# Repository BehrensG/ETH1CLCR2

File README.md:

<h1>ETH1CLCR2</h1>
LCR measurement card with Ethernet interface.

<h2>PCB Design</h2>

<p align="center">3D model rendition for PCB V1.0.</p>
<p align="center"></img></p>

<p align="center">Below are the images for the PCB V1.0. Mistake solved with botch wire.</p>

<p align="center"></img></p>
<p align="center"></img></p>
<p align="center"></img></p>

<h2>Tests</h2>
Some test measurements perform on passive components. 

>[!NOTE]
>The components where measured directly, not in a circuit. The cards was not calibrated.

<table align="center">
    <tr>
        <th>Type</th>
        <th>Component</th>
        <th>Value</th>
        <th>Component Tolerance</th>
        <th>Measurement</th>
    </tr>
    <tr>
        <td>Resistor</td>
        <td>WS21R000FEK</td>
        <td>2 Ω</td>
        <td>1%</td>
        <td>2.2352 Ω</td>
    </tr>
    <tr>
        <td>Resistor</td>
        <td>SR1206JR-7W3R3L</td>
        <td>3.3 Ω</td>
        <td>5%</td>
        <td>3.8283 Ω</td>
    </tr>
    <tr>
        <td>Resistor</td>
        <td>PTF5610K000AYEK</td>
        <td>10 kΩ</td>
        <td>0.05%</td>
        <td>10.01509 kΩ</td>
    </tr>
    <tr>
        <td>Resistor</td>
        <td>RN732BTTD9002B25</td>
        <td>90 kΩ</td>
        <td>0.1%</td>
        <td>90.02021 kΩ</td>
    </tr>
    <tr>
        <td>Resistor</td>
        <td>ERA-8VRB1003V</td>
        <td>100 kΩ</td>
        <td>0.1%</td>
        <td>100.294 kΩ</td>
    </tr>
    <tr>
        <td>Resistor</td>
        <td>HHV-50FR-52-10M</td>
        <td>10 MegΩ</td>
        <td>1%</td>
        <td>10.490122 MegΩ</td>
    </tr>
    <tr>
        <td>Inductor</td>
        <td>AISR-01-104J</td>
        <td>100 mH</td>
        <td>5%</td>
        <td>102.6 mH</td>
    </tr>
    <tr>
        <td>Capacitor</td>
        <td>KP1830310061</td>
        <td>10 nF</td>
        <td>1%</td>
        <td>10.07 nF</td>
    </tr>
    <tr>
        <td>Capacitor</td>
        <td>F461BC104F400A</td>
        <td>100 nF</td>
        <td>1%</td>
        <td>106 nF</td>
    </tr>
    <tr>
        <td>Capacitor</td>
        <td>C315C101F3G5TA</td>
        <td>0.1 nF</td>
        <td>1%</td>
        <td>0.1071 nF</td>
    </tr>
    <tr>
        <td>Capacitor</td>
        <td>D83W4010M01H</td>
        <td>10 uF</td>
        <td>3%</td>
        <td>10.152 uF</td>
    </tr>
    <tr>
        <td>Capacitor</td>
        <td>MPK1839510401</td>
        <td>1 uF</td>
        <td>1%</td>
        <td>1.0695 uF</td>
    </tr>
    <tr>
        <td>Capacitor</td>
        <td>EST108M063AM3AA</td>
        <td>1 mF</td>
        <td>20%</td>
        <td>1.1 mF</td>
    </tr>
    <tr>
        <td>Capacitor</td>
        <td>F463AG102F2K0A</td>
        <td>1 nF</td>
        <td>1%</td>
        <td>1.0459 nF</td>
    </tr>
    <tr>
        <td>Capacitor</td>
        <td>MKP1839310251</td>
        <td>10 nF</td>
        <td>1%</td>
        <td>10.0974 nF</td>
    </tr>
    <tr>
        <td>Capacitor</td>
        <td>MKP1837410011</td>
        <td>100 nF</td>
        <td>1%</td>
        <td>101.457 nF</td>
    </tr>
    <tr>
        <td>Capacitor</td>
        <td>23PS222</td>
        <td>2.2 nF</td>
        <td>5%</td>
        <td>2.2161 nF</td>
    </tr>
</table>

<h2>NOTES</h2>
The ETH1CLCR2 PCB works, but I don't recommend using this design. The design has mistakes and could be made simpler and better.

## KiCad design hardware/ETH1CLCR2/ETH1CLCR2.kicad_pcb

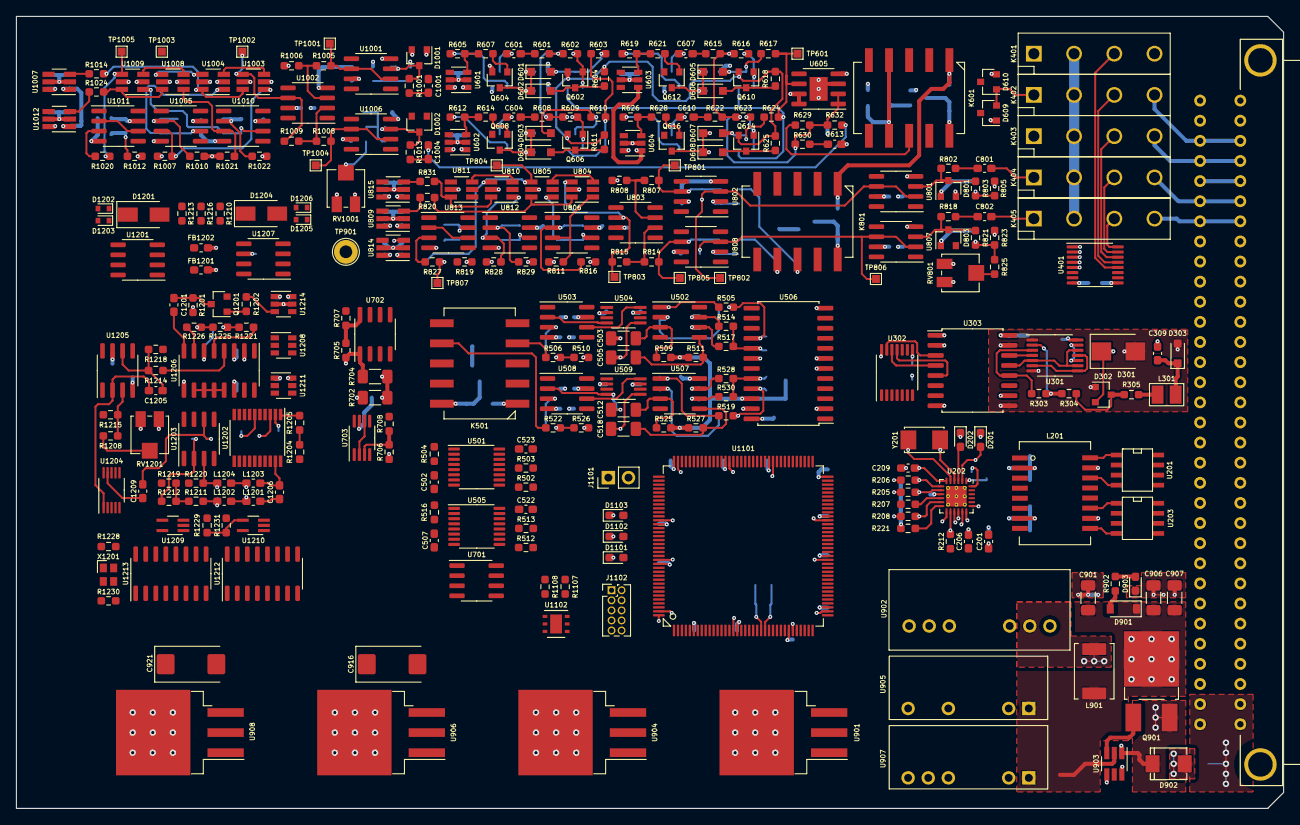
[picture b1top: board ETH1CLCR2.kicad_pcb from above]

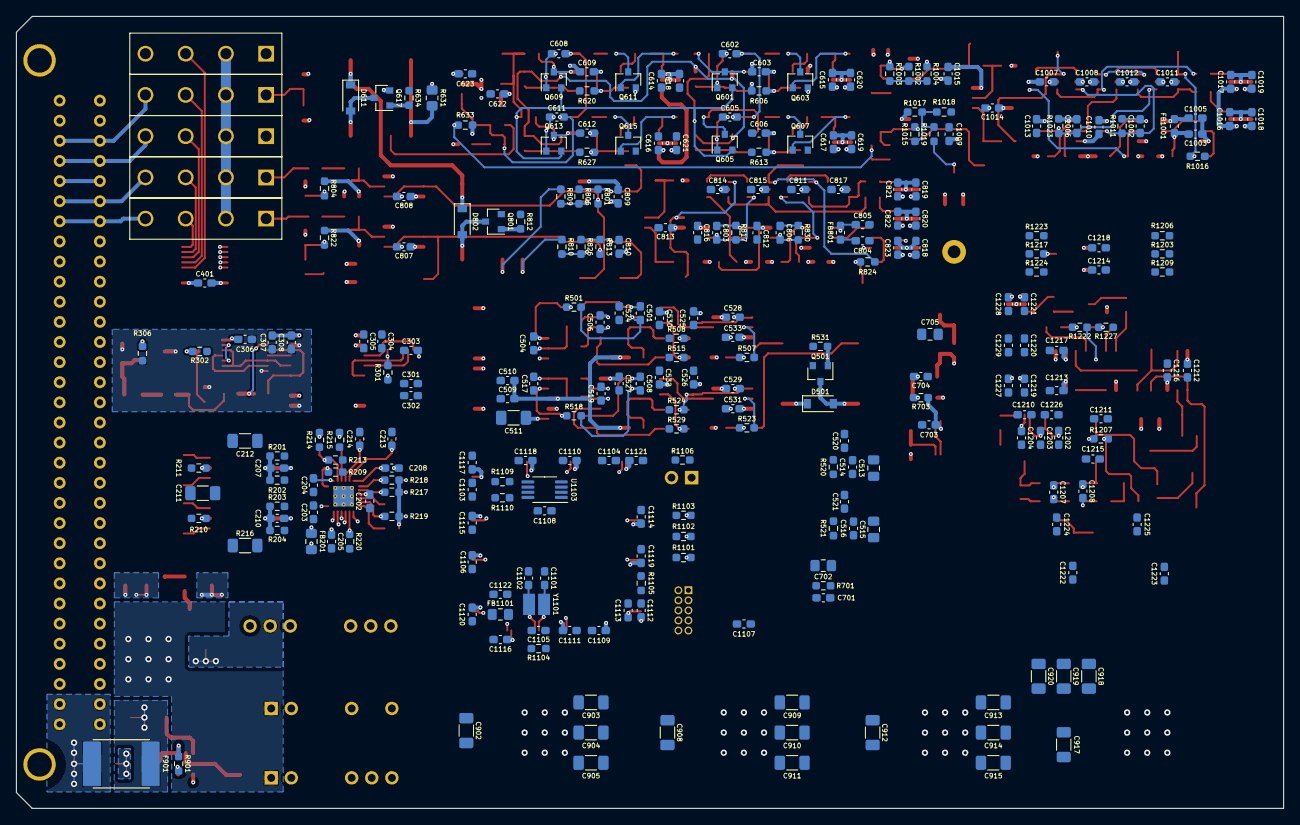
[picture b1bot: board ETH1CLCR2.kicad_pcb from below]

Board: 6 copper layers, 160.0 x 100.0 mm, 573 parts (268 on the bottom side), 354 nets.

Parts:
C201, C202, C204, C205, C206, C207, C210, C301, C303, C304, C306, C308, C520, C521, C522, C523, C524, C525, C526, C527, C528, C529, C530, C531, C532, C533, C603, C606, C609, C612, C614, C615, C616, C617, C618, C619, C620, C621, C622, C623, C807, C808, C809, C810, C811, C812, C813, C814, C815, C816, C817, C818, C819, C820, C821, C822, C823, C1007, C1008, C1009, C1010, C1011, C1012, C1013, C1014, C1015, C1016, C1017, C1018, C1019, C1105, C1107, C1108, C1109, C1110, C1111, C1112, C1113, C1114, C1115, C1116, C1117, C1118, C1119, C1120, C1121, C1203, C1210, C1211, C1212, C1213, C1214, C1215, C1216, C1217, C1218, C1219, C1220, C1221, C1222, C1223, C1224, C1225, C1226, C1227, C1228, C1229: 100n; C_0603_1608Metric_Pad1.08x0.95mm_HandSolder
C203, C209, C302, C305, C307, C401, C510, C514, C516, C701, C703, C704, C801, C802, C804, C805, C1001, C1003, C1004, C1005, C1106, C1122: 1u; C_0603_1608Metric_Pad1.08x0.95mm_HandSolder
C208, C613: 470p; C_0603_1608Metric_Pad1.08x0.95mm_HandSolder
C211, C212: 1n/1kV; C_1206_3216Metric_Pad1.33x1.80mm_HandSolder
C213, C214, C1101, C1102: 8p; C_0603_1608Metric_Pad1.08x0.95mm_HandSolder
C309: 47p; C_0603_1608Metric_Pad1.08x0.95mm_HandSolder
C501, C506, C508, C519: 470p/COG; C_0603_1608Metric_Pad1.08x0.95mm_HandSolder
C502, C507: 330p; C_0603_1608Metric_Pad1.08x0.95mm_HandSolder
C503, C505, C512, C518, C902, C903, C908, C909, C912, C913, C917, C918: 10u; C_1206_3216Metric_Pad1.33x1.80mm_HandSolder
C504, C517: 2700p/COG; C_0603_1608Metric_Pad1.08x0.95mm_HandSolder
C509, C1201: 10n; C_0603_1608Metric_Pad1.08x0.95mm_HandSolder
C511: 47u; C_1206_3216Metric_Pad1.33x1.80mm_HandSolder
C513, C515: 22u; C_0805_2012Metric_Pad1.18x1.45mm_HandSolder
C601, C604: 4n7; C_0603_1608Metric_Pad1.08x0.95mm_HandSolder
C602, C605, C607, C608, C610, C611, C803, C806, C1002, C1006: DNP; C_0603_1608Metric_Pad1.08x0.95mm_HandSolder
C702, C705: 10u; C_0805_2012Metric_Pad1.18x1.45mm_HandSolder
C901: 4u7; C_1206_3216Metric_Pad1.33x1.80mm_HandSolder
C904, C910, C914, C919: 1u; C_1206_3216Metric_Pad1.33x1.80mm_HandSolder
C905, C911, C915, C920: 100n; C_1206_3216Metric_Pad1.33x1.80mm_HandSolder
C906, C907: 4u7/50V; C_1206_3216Metric_Pad1.33x1.80mm_HandSolder
C916, C921: T521V107M016ATE050; CP_EIA-7343-20_Kemet-V_Pad2.25x2.55mm_HandSolder
C1103, C1104: 2u2; C_0603_1608Metric_Pad1.08x0.95mm_HandSolder
C1202, C1204, C1209: 4u7; C_0603_1608Metric_Pad1.08x0.95mm_HandSolder
C1205: 3p3/COG; C_0603_1608Metric_Pad1.08x0.95mm_HandSolder
C1206, C1208: 100p; C_0603_1608Metric_Pad1.08x0.95mm_HandSolder
C1207: 68p; C_0603_1608Metric_Pad1.08x0.95mm_HandSolder
D201: YELLOW; LED_0603_1608Metric_Pad1.05x0.95mm_HandSolder
D202, D1102: GREEN; LED_0603_1608Metric_Pad1.05x0.95mm_HandSolder
D301: SMBJ5.0A; D_SMB
D302: BAV99; SOT-23
D303: SD36C-01FTG; D_SOD-323_HandSoldering
D501, D611, D802: 1N4148W; D_SOD-123
D601, D602, D603, D604, D605, D606, D607, D608: BAS16J; D_SOD-323_HandSoldering
D609, D610, D801, D803, D1001, D1002: BAV199; SOT-23
D901: MMSZ5249B; D_SOD-123
D902: SM6T30AY; DO_214AA_REV
D903, D1101: RED; LED_0603_1608Metric_Pad1.05x0.95mm_HandSolder
D1103: BLUE; LED_0603_1608Metric_Pad1.05x0.95mm_HandSolder
D1201, D1204: BYG20J; D_SMA
D1202, D1203, D1205, D1206: BZX584C5V6; D_SOD-523
F901: MF-LSMF185/33X; Fuse_SMD2920
FB201, FB1101: 742792031; L_0805_2012Metric_Pad1.15x1.40mm_HandSolder
FB801, FB1001: BLM18TG102TN1D; L_0603_1608Metric_Pad1.05x0.95mm_HandSolder
FB1201, FB1202: BLM18SP601SZ1D; L_0603_1608Metric_Pad1.05x0.95mm_HandSolder
J401: C64AC; Socket_DIN41612-CaseC1-AC-Male-64Pin-2rows
J1101: Conn_02x01; PinHeader_1x02_P2.54mm_Vertical
J1102: 20021111-00010T4LF; PinHeader_2x05_P1.27mm_Vertical
K401, K402, K403, K404, K405: HE3621A0510; HE360_x-5050462-8
K501, K601, K801: TQ2SA-5V; SA
L201: 749010012A
L301: CW252016-R33G; CW252016
L901: PM1608S-100M-RC; PM1608S
L1201, L1202, L1203, L1204: CBMF1608T100K; L_0603_1608Metric_Pad1.05x0.95mm_HandSolder
Q501, Q603, Q607, Q611, Q615, Q617, Q801: BC847; SOT-23
Q601, Q602, Q605, Q606, Q609, Q610, Q613, Q614: MMBFJ309LT1G; SOT-23
Q604, Q608, Q612, Q616: BC857; SOT-23
Q901: IRFR5410; TO-252-2_Rectifier
Q1201: FDV301N; SOT-23
R201, R202, R203, R204: 49R9; R_0603_1608Metric_Pad0.98x0.95mm_HandSolder
R205, R206, R208, R212, R1227: 33; R_0603_1608Metric_Pad0.98x0.95mm_HandSolder
R207, R213, R217, R218, R219, R220, R301, R502, R503, R509, R511, R512, R513, R525, R527, R606, R613, R620, R627, R634, R812, R1104, R1105, R1106: 10k; R_0603_1608Metric_Pad0.98x0.95mm_HandSolder
R209: 12k1; R_0603_1608Metric_Pad0.98x0.95mm_HandSolder
R210, R211: 75/1%; R_0603_1608Metric_Pad0.98x0.95mm_HandSolder
R214, R215: 270; R_0603_1608Metric_Pad0.98x0.95mm_HandSolder
R216: 1M/1kV; R_1206_3216Metric_Pad1.30x1.75mm_HandSolder
R221: 1k5; R_0603_1608Metric_Pad0.98x0.95mm_HandSolder
R302, R820, R831, R1014, R1024, R1228: 1k; R_0603_1608Metric_Pad0.98x0.95mm_HandSolder
R303: 14k7; R_0603_1608Metric_Pad0.98x0.95mm_HandSolder
R304, R819, R1012, R1206, R1222, R1223: 100; R_0603_1608Metric_Pad0.98x0.95mm_HandSolder
R305: 47; R_0603_1608Metric_Pad0.98x0.95mm_HandSolder
R306: 51R1; R_0603_1608Metric_Pad0.98x0.95mm_HandSolder
R501, R517, R518, R530: 634; R_0603_1608Metric_Pad0.98x0.95mm_HandSolder
R504, R516, R632: 0; R_0603_1608Metric_Pad0.98x0.95mm_HandSolder
R505, R514, R519, R528: 91; R_0603_1608Metric_Pad0.98x0.95mm_HandSolder
R506, R510, R522, R526, R616: 10k/.1%; R_0603_1608Metric_Pad0.98x0.95mm_HandSolder
R507, R523: 300; R_0603_1608Metric_Pad0.98x0.95mm_HandSolder
R508, R515, R524, R529, R901, R1201, R1208: 100k; R_0603_1608Metric_Pad0.98x0.95mm_HandSolder
R520, R521, R701: 0R22; R_0603_1608Metric_Pad0.98x0.95mm_HandSolder
R531, R605, R607, R612, R614, R619, R621, R626, R628: 10K; R_0603_1608Metric_Pad0.98x0.95mm_HandSolder
R601, R608: 33/.1%; R_0603_1608Metric_Pad0.98x0.95mm_HandSolder
R602, R629, R802, R818, R1001, R1013: 100/.1%; R_0603_1608Metric_Pad0.98x0.95mm_HandSolder
R603, R604, R610, R611, R617, R618, R624, R625, R803, R821, R1002, R1015: 1Meg; R_0603_1608Metric_Pad0.98x0.95mm_HandSolder
R609, R807, R808, R814, R815, R1005, R1006, R1008, R1009: 1k/.1%; R_0603_1608Metric_Pad0.98x0.95mm_HandSolder
R615, R622, R633, R801, R813, R824, R1016: DNP; R_0603_1608Metric_Pad0.98x0.95mm_HandSolder
R623, R811, R828, R1007, R1021: 100k/.1%; R_0603_1608Metric_Pad0.98x0.95mm_HandSolder
R630: 47/.1%; R_0603_1608Metric_Pad0.98x0.95mm_HandSolder
R631: 0R1; R_0805_2012Metric_Pad1.20x1.40mm_HandSolder
R702: 3R3/.5W; R_1206_3216Metric_Pad1.30x1.75mm_HandSolder
R703: 10; R_0603_1608Metric_Pad0.98x0.95mm_HandSolder
R704: 33/.5W; R_1206_3216Metric_Pad1.30x1.75mm_HandSolder
R705: 220/.1%; R_0603_1608Metric_Pad0.98x0.95mm_HandSolder
R706, R708, R827, R1020: 3k3/.1%; R_0603_1608Metric_Pad0.98x0.95mm_HandSolder
R707: 1k1/.1%; R_0603_1608Metric_Pad0.98x0.95mm_HandSolder
R804, R805, R816, R822, R823, R829, R1003, R1004, R1010, R1017, R1018, R1022: 2k/.1%; R_0603_1608Metric_Pad0.98x0.95mm_HandSolder
R806, R826: 1k8/.1%; R_0603_1608Metric_Pad0.98x0.95mm_HandSolder
R809, R810: 200/.1%; R_0603_1608Metric_Pad0.98x0.95mm_HandSolder
R817, R830, R1011, R1023: 18k/.1%; R_0603_1608Metric_Pad0.98x0.95mm_HandSolder
R825, R1019: 47k/.1%; R_0603_1608Metric_Pad0.98x0.95mm_HandSolder
R902, R1209, R1219, R1224: 330; R_0603_1608Metric_Pad0.98x0.95mm_HandSolder
R1101, R1103, R1203, R1217, R1218: 680; R_0603_1608Metric_Pad0.98x0.95mm_HandSolder
R1102: 560; R_0603_1608Metric_Pad0.98x0.95mm_HandSolder
R1107, R1108, R1109, R1110, R1202: 4k7; R_0603_1608Metric_Pad0.98x0.95mm_HandSolder
R1204: 6k8; R_0603_1608Metric_Pad0.98x0.95mm_HandSolder
R1205: 2k; R_0603_1608Metric_Pad0.98x0.95mm_HandSolder
R1207: 820; R_0603_1608Metric_Pad0.98x0.95mm_HandSolder
R1210, R1213, R1216: 150; R_0603_1608Metric_Pad0.98x0.95mm_HandSolder
R1211, R1212, R1215, R1220, R1226: 200; R_0603_1608Metric_Pad0.98x0.95mm_HandSolder
R1214, R1221: 220; R_0603_1608Metric_Pad0.98x0.95mm_HandSolder
R1225, R1229, R1230, R1231: 68; R_0603_1608Metric_Pad0.98x0.95mm_HandSolder
RV801, RV1001: 3314J-1-203E; Potentiometer_Bourns_3314J_Vertical
RV1201: 3314J-1-104E; Potentiometer_Bourns_3314J_Vertical
TP601, TP801, TP802, TP803, TP804, TP805, TP806, TP807, TP1001, TP1002, TP1003, TP1004, TP1005: TestPoint; TestPoint_Pad_1.0x1.0mm
TP901: TestPoint; TestPoint_Loop_D2.60mm_Drill1.6mm_Beaded
U201, U203: LC03-3.3; SO8E
U202: LAN8742A; QFN-24-1EP_4x4mm_P0.5mm_EP2.6x2.6mm_ThermalVias
U301: 74AC125; TSSOP-14_4.4x5mm_P0.65mm
U302: TXB0104PW; TSSOP-14_4.4x5mm_P0.65mm
U303: ADuM5402; SOIC-16W_7.5x10.3mm_P1.27mm
U401: ULN2003A; TSSOP-16_4.4x5mm_P0.65mm
U501, U505: ADS8681PWR; TSSOP-16_4.4x5mm_P0.65mm
U502, U507: AD8656; SOIC-8_3.9x4.9mm_P1.27mm
U503, U508: OP1177AR; SOIC-8_3.9x4.9mm_P1.27mm
U504, U509: AD8476_MSOP; MSOP-8_3x3mm_P0.65mm
U506: CS5361; SOIC-24W_7.5x15.4mm_P1.27mm
U601, U602, U603, U604, U1208, U1211, U1214: SN74LVC1T45DBV; SOT-23-6
U605: ADA4817-1ARDZ; SOIC-8-1EP_3.9x4.9mm_P1.27mm_EP2.29x3mm
U701: REF5040ID; SOIC-8_3.9x4.9mm_P1.27mm
U702: TL431BCDE4; SOIC-8_3.9x4.9mm_P1.27mm
U703: MCP6L91RT-EMS; MSOP-8_3x3mm_P0.65mm
U801, U807, U813, U1001, U1006, U1011: MCP6L91RT-ESN; SOIC-8_3.9x4.9mm_P1.27mm
U802, U803, U806, U808, U812, U1002, U1005, U1010: MCP661; SOIC-8_3.9x4.9mm_P1.27mm
U804, U805, U810, U811, U1003, U1004, U1008, U1009: SN74LVC1G3157; SOT-23-6_Handsoldering
U809, U814, U815, U1007, U1012: SN74LVC1T45DBV; SOT-23-6_Handsoldering
U901: TLV1117-33; TO-263-3_TabPin2
U902: NCS3S1205SC; NCS3
U903: MAX5902; SOT-23-6_Handsoldering
U904, U906: TLV1117-50; TO-263-3_TabPin2
U905: NMK2409SAC; NMK_SINGLE
U907: NMK2409SC; NMK_DUAL
U908: LM2990SX-5.0; TO-263-3_TabPin2
U1101: STM32H743ZI; TQFP-144_20x20mm_P0.5mm
U1102: HDC1080; Texas_PWSON-N6
U1103: 24LC08B-E/MS; MSOP-8_3x3mm_P0.65mm
U1201, U1207: LMH6639; SOIC-8_3.9x4.9mm_P1.27mm
U1202: AD9834; TSSOP-20_4.4x6.5mm_P0.65mm
U1203, U1205: AD8038; SOIC-8_3.9x4.9mm_P1.27mm
U1204: DAC7811; VSSOP-10_3x3mm_P0.5mm
U1206: DG409; SOIC-16_3.9x9.9mm_P1.27mm
U1209: 74AHC1G14; SOT-353_SC-70-5_Handsoldering
U1210: 74AUP1G79; SOT-353_SC-70-5_Handsoldering
U1212, U1213: 74AC161; SOIC-16_3.9x9.9mm_P1.27mm
X1201: 830208220601; IQXO-791
Y201: NX5032GA-25.000M-LN-CD-1; NX5032GA
Y1101: NX3225GD-8MHZ; NX3225GD

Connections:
+1V5: R808.1, R811.2, R816.2, R828.2, R829.2, R1006.1, R1007.2, R1010.2, R1021.2, R1022.2, U703.2, U703.6
+3.3VP: C705.1, R704.1, R705.1, R706.1, R805.1, R823.1, R1004.1, R1018.1, RV801.1, RV1001.1, U702.1
+3V3: C201.1, C202.1, C301.1, C302.1, C522.1, C523.1, C618.1, C619.1, C620.1, C621.1, C818.1, C819.1, C820.1, C903.1, C904.1, C905.1, C1018.1, C1019.1, C1106.1, C1107.1, C1108.1, C1109.1, C1110.1, C1111.1, C1112.1, C1113.1, C1114.1, C1115.1, C1116.1, C1117.1, C1118.1, C1119.1, C1120.1, C1121.1, C1222.1, C1223.1, C1224.1, C1225.1, C1226.1, C1227.1, C1228.1, C1229.1, D1101.2, D1102.2, D1103.2, FB201.2, FB1101.2, J1102.1, R217.1, R218.1, R219.1, R220.1, R221.1, R301.1, R502.1, R503.1, R512.1, R513.1, R702.1, R1104.1, R1106.2, R1107.1, R1108.1, R1109.1, R1110.1, R1228.1, U202.9, U302.1, U501.16, U505.16, U506.2, U506.6, U506.8, U506.12, U601.6, U602.6, U603.6, U604.6, U809.6, U814.6, U815.6, U901.2, U1007.6, U1012.6, U1101.6, U1101.17, U1101.30, U1101.39, U1101.52, U1101.62, U1101.72, U1101.84, U1101.95, U1101.108, U1101.121, U1101.131, U1101.143, U1101.144, U1102.5, U1103.8, U1202.5, U1204.8, U1208.6, U1209.5, U1210.5, U1211.6, U1212.1, U1212.7, U1212.10, U1212.16, U1213.1, U1213.3, U1213.6, U1213.7, U1213.16, U1214.6, X1201.4
+4V: R701.1, U501.4, U505.4, U701.6
+5V: C303.1, C304.1, C305.1, C401.1, C520.1, C521.1, C614.1, C615.1, C616.1, C617.1, C821.1, C822.1, C823.1, C909.1, C910.1, C911.1, C1016.1, C1017.1, C1219.1, C1220.1, C1221.1, D501.1, D611.1, D802.1, K401.2, K402.2, K403.2, K404.2, K405.2, K501.1, K601.1, K801.1, U302.14, U303.1, U401.9, U501.2, U505.2, U506.19, U601.1, U602.1, U603.1, U604.1, U701.2, U809.1, U814.1, U815.1, U904.2, U1007.1, U1012.1, U1208.1, U1211.1, U1214.1
+5VA: C524.1, C525.1, C526.1, C527.1, C528.1, C529.1, C622.1, C807.1, C808.1, C809.1, C810.1, C811.1, C812.1, C813.1, C814.1, C815.1, C816.1, C817.1, C913.1, C914.1, C915.1, C916.1, C1007.1, C1008.1, C1009.1, C1010.1, C1011.1, C1012.1, C1013.1, C1014.1, C1015.1, C1210.1, C1211.1, C1212.1, C1213.1, C1214.1, D801.2, D803.2, D1001.2, D1002.2, D1201.1, D1202.1, D1203.1, FB1201.1, Q604.2, Q608.2, Q612.2, Q616.2, R819.2, R1012.2, R1201.1, RV1201.1, U502.8, U503.7, U504.2, U507.8, U508.7, U509.2, U605.7, U605.8, U801.7, U802.7, U803.7, U804.5, U805.5, U806.7, U807.7, U808.7, U810.5, U811.5, U812.7, U906.2, U1001.7, U1002.7, U1003.5, U1004.5, U1005.7, U1006.7, U1008.5, U1009.5, U1010.7, U1201.8, U1202.4, U1203.7, U1205.7, U1206.2, U1206.14, U1207.8
+5V_TRIG: C306.1, C307.1, C308.1, R302.1, U301.14, U303.10, U303.16
+24V: F901.2, J401.A31, J401.A32, J401.C31, J401.C32
-5VA: C530.1, C531.1, C532.1, C533.1, C623.1, C918.2, C919.2, C920.2, C921.2, C1215.1, C1216.1, C1217.1, C1218.1, D1204.2, D1205.2, D1206.2, FB1202.1, R606.2, R613.2, R620.2, R627.2, RV1201.3, U503.4, U504.7, U508.4, U509.7, U605.4, U908.3, U1203.4, U1205.4, U1206.3
/ADC/ADC1_IIN: K501.2, R504.2
/ADC/ADC1_MISO: R513.2, U505.13, U1101.112
/ADC/ADC1_MOSI: U501.10, U1101.113
/ADC/ADC1_RVS1: U501.15, U1101.114
/ADC/ADC1_RVS2: U505.15, U1101.115
/ADC/ADC1_SCLK: U501.12, U505.12, U1101.111
/ADC/ADC1_VIN: K501.9, R516.2
/ADC/ADC1_~CS: U501.11, U505.11, U1101.110
/ADC/ADC2_IIN: K501.4, R506.2
/ADC/ADC2_VIN: K501.7, R522.2
/ADC/ADC_IIN: K501.3, U1011.2, U1011.6
/ADC/ADC_VIN: K501.8, U813.2, U813.6
/ADC/CAP1: R520.1, U501.6
/ADC/CAP2: R521.1, U505.6
/ADC/DDS_CLK: R1231.1, U506.5
/ADC/VQ: C509.1, C510.1, R509.2, R511.2, R525.2, R527.2, U506.22
/Connector/A: J401.A2, J401.C2, K401.4
/Connector/B: J401.A3, J401.C3, K402.4
/Connector/C: J401.A4, J401.C4, K403.4
/Connector/CXN_REL1: U401.5, U1101.122
/Connector/CXN_REL2: U401.4, U1101.119
/Connector/CXN_REL3: U401.3, U1101.118
/Connector/CXN_REL4: U401.2, U1101.117
/Connector/CXN_REL5: U401.1, U1101.116
/Connector/D: J401.A5, J401.C5
/Connector/E: J401.A6, J401.C6, K404.4
/Connector/EXT_TRIG: C309.1, D303.1, J401.A16, L301.1
/Connector/F: J401.A7, J401.C7, K405.4
/Connector/H_CUR: K401.1, R1210.1, R1213.1, R1216.1
/Connector/H_POT: C801.2, K404.1
/Connector/L_CUR: D609.2, D610.1, K402.1, K601.3
/Connector/L_POT: C802.2, K405.1
/Connector/RX+: J401.A20, U203.8
/Connector/RX-: J401.A21, U203.5
/Connector/TX+: J401.C20, U201.8
/Connector/TX-: J401.C21, U201.5
/Current Diff Amp/CUR_IN: C1001.2, Q602.2, Q606.2, Q610.2, Q614.2, R604.1, R611.1, R618.1, R625.1
/Current Diff Amp/CUR_ZERO: C1004.2, R632.1, R633.1
/Current Diff Amp/IDIFF0: U1012.4, U1101.139
/Current Diff Amp/IDIFF1: U1007.4, U1101.140
/DDS/A0: U1206.1, U1208.3
/DDS/A1: U1206.16, U1211.3
/DDS/DDS_CS: U1101.73, U1202.15
/DDS/DDS_SCLK: U1101.74, U1202.14
/DDS/DDS_SDATA: U1101.76, U1202.13
/DDS/LPF: R1202.2, U1214.3
/DDS/MCLK: R1229.1, U1202.8
/DDS/MDAC_CS: U1101.40, U1204.6
/DDS/MDAC_SCK: U1101.41, U1204.4
/DDS/MDAC_SDIN: U1101.123, U1204.5
/DDS/MDAC_SDO: U1101.42, U1204.7
/DDS/~DDS_DIV10: U1213.4, U1213.5
/Ethernet/ETH_RXN: L201.8, R204.2, U202.22
/Ethernet/ETH_RXP: L201.6, R203.2, U202.23
/Ethernet/ETH_TXN: L201.3, R202.2, U202.20
/Ethernet/ETH_TXP: L201.1, R201.2, U202.21
/Ethernet/MODE0: R205.1, R217.2, U202.8
/Ethernet/MODE1: R206.1, R218.2, U202.7
/Ethernet/MODE2: R208.1, R219.2, U202.11
/Ethernet/NRST: C1105.1, J1102.10, R1104.2, U202.15, U1101.25
/Ethernet/REFCLK0: R212.1, R220.2, U202.14
/Ethernet/REF_CLK: R212.2, U1101.35
/Ethernet/RMII_CRS_DV: R208.2, U1101.43
/Ethernet/RMII_MDC: U202.13, U1101.27
/Ethernet/RMII_MDIO: R221.2, U202.12, U1101.36
/Ethernet/RMII_RXD0: R205.2, U1101.44
/Ethernet/RMII_RXD1: R206.2, U1101.45
/Ethernet/RMII_TXD0: U202.17, U1101.128
/Ethernet/RMII_TXD1: U202.18, U1101.129
/Ethernet/RMII_TXEN: U202.16, U1101.126
/I/V Converter/IRR0: R634.2, U1101.133
/I/V Converter/IRR1: U601.4, U1101.134
/I/V Converter/IRR2: U602.4, U1101.135
/I/V Converter/IRR3: U603.4, U1101.136
/I/V Converter/IRR4: U604.4, U1101.137
/MCU/EEPROM_SCL: R1110.2, U1101.81, U1103.6
/MCU/EEPROM_SDA: R1109.2, U1101.82, U1103.5
/MCU/EEPROM_WP: U1101.80, U1103.7
/MCU/MCU_DEFAULT: J1101.1, R1106.1, U1101.37
/MCU/MCU_VDDA: C1122.1, FB1101.1, U1101.32, U1101.33
/MCU/SENS_SCL: R1107.2, U1101.100, U1102.6
/MCU/SENS_SDA: R1108.2, U1101.99, U1102.1
/MCU/TCK_SWCLK: J1102.4, U1101.109
/MCU/TMS_SWDIO: J1102.2, U1101.105
/MCU/TRIG_EN: U302.2, U1101.92
/MCU/TRIG_IN: U302.4, U1101.88
/MCU/TRIG_OUT: U302.3, U1101.91
/MCU/VDIFF0: U814.4, U1101.46
/MCU/VDIFF1: U815.4, U1101.47
/MCU/VDIFF2: U809.4, U1101.48
/Trigger/EXT_TRIG_SIGN: R303.1, U301.3, U303.12
/Trigger/TRIG_OUT_EN: U301.4, U301.10, U301.13, U303.14
/Trigger/TRIG_OUT_SIGN: U301.5, U301.9, U301.12, U303.13
Earth: C211.2, C212.1, J401.A18, J401.A22, J401.C18, J401.C22, R216.1
GND: C201.2, C202.2, C203.2, C204.2, C205.2, C206.2, C207.2, C208.2, C209.2, C210.2, C212.2, C213.2, C214.2, C301.2, C302.2, C303.2, C304.2, C305.2, C401.2, C502.2, C507.2, C509.2, C510.2, C511.2, C513.2, C514.2, C515.2, C516.2, C520.2, C521.2, C522.2, C523.2, C524.2, C525.2, C526.2, C527.2, C528.2, C529.2, C530.2, C531.2, C532.2, C533.2, C603.2, C606.2, C609.2, C612.2, C613.2, C614.2, C615.2, C616.2, C617.2, C618.2, C619.2, C620.2, C621.2, C622.2, C623.2, C701.2, C702.2, C703.2, C704.2, C705.2, C804.1, C805.1, C807.2, C808.2, C809.2, C810.2, C811.2, C812.2, C813.2, C814.2, C815.2, C816.2, C817.2, C818.2, C819.2, C820.2, C821.2, C822.2, C823.2, C902.2, C903.2, C904.2, C905.2, C908.2, C909.2, C910.2, C911.2, C912.2, C913.2, C914.2, C915.2, C916.2, C917.1, C918.1, C919.1, C920.1, C921.1, C1003.1, C1005.1, C1007.2, C1008.2, C1009.2, C1010.2, C1011.2, C1012.2, C1013.2, C1014.2, C1015.2, C1016.2, C1017.2, C1018.2, C1019.2, C1101.2, C1102.2, C1103.2, C1104.2, C1105.2, C1106.2, C1107.2, C1108.2, C1109.2, C1110.2, C1111.2, C1112.2, C1113.2, C1114.2, C1115.2, C1116.2, C1117.2, C1118.2, C1119.2, C1120.2, C1121.2, C1122.2, C1202.2, C1203.1, C1204.1, C1210.2, C1211.2, C1212.2, C1213.2, C1214.2, C1215.2, C1216.2, C1217.2, C1218.2, C1219.2, C1220.2, C1221.2, C1222.2, C1223.2, C1224.2, C1225.2, C1226.2, C1227.2, C1228.2, C1229.2, D609.1, D610.2, D801.1, D803.1, D1001.1, D1002.1, D1202.2, D1203.2, D1205.1, D1206.1, J1101.2, J1102.3, J1102.5, K403.1, Q501.2, Q603.2, Q607.2, Q611.2, Q615.2, Q617.2, Q801.2, Q1201.2, R207.2, R209.1, R213.2, R214.2, R215.2, R216.2, R508.2, R510.1, R515.2, R524.2, R526.1, R529.2, R631.2, R633.2, R707.2, R708.2, R804.2, R822.2, R1003.2, R1017.2, R1105.2, R1204.1, R1209.2, R1215.2, R1219.2, R1220.2, R1224.2, R1227.2, RV801.3, RV1001.3, TP901.1, U202.25, U302.7, U303.2, U303.8, U401.8, U501.1, U501.3, U501.5, U501.8, U502.4, U504.1, U504.3, U505.1, U505.3, U505.5, U505.8, U506.7, U506.18, U506.23, U507.4, U509.1, U509.3, U601.2, U601.5, U602.2, U602.5, U603.2, U603.5, U604.2, U604.5, U605.3, U605.9, U701.4, U702.2, U702.3, U702.6, U702.7, U703.4, U801.4, U802.4, U803.4, U804.2, U805.2, U806.4, U807.4, U808.4, U809.2, U809.5, U810.2, U811.2, U812.4, U813.4, U814.2, U814.5, U815.2, U815.5, U901.1, U902.7, U904.1, U905.5, U906.1, U907.6, U908.1, U1001.4, U1002.4, U1003.2, U1004.2, U1005.4, U1006.4, U1007.2, U1007.5, U1008.2, U1009.2, U1010.4, U1011.4, U1012.2, U1012.5, U1101.16, U1101.31, U1101.38, U1101.51, U1101.61, U1101.83, U1101.94, U1101.107, U1101.120, U1101.130, U1102.2, U1103.1, U1103.2, U1103.3, U1103.4, U1202.7, U1202.9, U1202.10, U1202.11, U1202.12, U1202.17, U1202.18, U1204.2, U1204.3, U1206.9, U1206.15, U1208.2, U1208.5, U1209.3, U1210.3, U1211.2, U1211.5, U1212.3, U1212.8, U1213.8, U1214.2, U1214.5, X1201.2
GNDPWR: C901.2, C906.2, C907.2, D902.2, D903.1, J401.A27, J401.A28, J401.C27, J401.C28, U902.1, U903.4, U905.2, U907.2
GND_TRIG: C306.2, C307.2, C308.2, D301.2, D302.1, D303.2, J401.C16, R306.2, U301.1, U301.7, U303.9, U303.15
unnamed: C208.1, C209.1, U202.6
unnamed: C211.1, R210.2, R211.2
unnamed: C213.1, U202.5, Y201.2
unnamed: C214.1, U202.4, Y201.1
unnamed: C309.2, R306.1
unnamed: C501.1, R505.2, U502.1
unnamed: C501.2, R501.2, U502.2
unnamed: C502.1, R504.1, U501.7
unnamed: C503.1, R509.1, U502.3
unnamed: C503.2, R508.1, U503.2, U504.4
unnamed: C504.1, R501.1, R505.1, U506.16
unnamed: C504.2, R514.1, R517.1, U506.17
unnamed: C505.1, R511.1, U502.5
unnamed: C505.2, R515.1, U504.5
unnamed: C506.1, R514.2, U502.7
unnamed: C506.2, R517.2, U502.6
unnamed: C507.1, R516.1, U505.7
unnamed: C508.1, R519.2, U507.1
unnamed: C508.2, R518.2, U507.2
unnamed: C511.1, U506.24
unnamed: C512.1, R525.1, U507.3
unnamed: C512.2, R524.1, U508.2, U509.4
unnamed: C513.1, C514.1, R520.2
unnamed: C515.1, C516.1, R521.2
unnamed: C517.1, R518.1, R519.1, U506.21
unnamed: C517.2, R528.1, R530.1, U506.20
unnamed: C518.1, R527.1, U507.5
unnamed: C518.2, R529.1, U509.5
unnamed: C519.1, R528.2, U507.7
unnamed: C519.2, R530.2, U507.6
unnamed: C601.1, R601.2
unnamed: C601.2, Q603.3
unnamed: C602.1, Q601.1, Q602.1, R602.1
unnamed: C602.2, C605.2, C608.2, C611.2, K601.2, R601.1, R602.2, R608.1, R609.2, R615.1, R616.2, R622.1, R623.2, R629.1, R630.1, R632.2, U605.1, U605.2
unnamed: C603.1, D601.1, D602.1, Q604.3, R606.1
unnamed: C604.1, R608.2
unnamed: C604.2, Q607.3
unnamed: C605.1, Q605.1, Q606.1, R609.1
unnamed: C606.1, D603.1, D604.1, Q608.3, R613.1
unnamed: C607.1, R615.2
unnamed: C607.2, Q611.3
unnamed: C608.1, Q609.1, Q610.1, R616.1
unnamed: C609.1, D605.1, D606.1, Q612.3, R620.1
unnamed: C610.1, R622.2
unnamed: C610.2, Q615.3
unnamed: C611.1, Q613.1, Q614.1, R623.1
unnamed: C612.1, D607.1, D608.1, Q616.3, R627.1
unnamed: C613.1, R630.2
unnamed: C701.1, U701.5
unnamed: C702.1, R701.2
unnamed: C703.1, R703.1, U703.7
unnamed: C704.1, R702.2, R703.2, R704.2
unnamed: C801.1, R802.2
unnamed: C802.1, R818.2
unnamed: C803.1, R817.1, U805.1, U806.6
unnamed: C803.2, R816.1, R817.2, U806.2
unnamed: C804.2, FB801.1, R819.1
unnamed: C805.2, FB801.2, U813.7
unnamed: C806.1, R830.1, U811.1, U812.6
unnamed: C806.2, R829.1, R830.2, U812.2
unnamed: C901.1, C906.1, C907.1, D901.1, L901.1, Q901.2, U903.2, U905.1, U907.1
unnamed: C902.1, U901.3, U902.6
unnamed: C908.1, U904.3, U905.7
unnamed: C912.1, U906.3, U907.7
unnamed: C917.2, U907.5, U908.2
unnamed: C1001.1, R1001.2
unnamed: C1002.1, R1011.1, U1004.1, U1005.6
unnamed: C1002.2, R1010.1, R1011.2, U1005.2
unnamed: C1003.2, FB1001.1, R1012.1
unnamed: C1004.1, R1013.2
unnamed: C1005.2, FB1001.2, U1011.7
unnamed: C1006.1, R1023.1, U1009.1, U1010.6
unnamed: C1006.2, R1022.1, R1023.2, U1010.2
unnamed: C1101.1, U1101.23, Y1101.1
unnamed: C1102.1, U1101.24, Y1101.2
unnamed: C1103.1, U1101.71
unnamed: C1104.1, U1101.106
unnamed: C1201.1, U1201.3, U1206.8, U1207.3
unnamed: C1201.2, Q1201.3, R1201.2
unnamed: C1202.1, U1202.6
unnamed: C1203.2, U1202.3
unnamed: C1204.2, U1202.2
unnamed: C1205.1, R1214.2, R1218.2, U1204.10, U1205.6
unnamed: C1205.2, U1204.1, U1205.2
unnamed: C1206.1, L1201.1, U1202.20
unnamed: C1206.2, L1203.1, U1202.19
unnamed: C1207.1, L1201.2, L1202.1
unnamed: C1207.2, L1203.2, L1204.1
unnamed: C1208.1, L1202.2, R1211.2
unnamed: C1208.2, L1204.2, R1220.1, U1203.3
unnamed: C1209.1, U1204.9
unnamed: C1209.2, R1207.1, U1203.6
unnamed: D201.1, R214.1
unnamed: D201.2, R213.1, U202.2
unnamed: D202.1, R215.1
unnamed: D202.2, U202.3
unnamed: D301.1, D302.2, R302.2
unnamed: D302.3, R304.2, R305.1, U301.6, U301.8, U301.11
unnamed: D501.2, K501.10, Q501.3
unnamed: D601.2, Q601.3, R603.2
unnamed: D602.2, Q602.3, R604.2
unnamed: D603.2, Q605.3, R610.2
unnamed: D604.2, Q606.3, R611.2
unnamed: D605.2, Q609.3, R617.2
unnamed: D606.2, Q610.3, R618.2
unnamed: D607.2, Q613.3, R624.2
unnamed: D608.2, Q614.3, R625.2
unnamed: D611.2, K601.10, Q617.3
unnamed: D801.3, R802.1, R803.2, U801.3
unnamed: D802.2, K801.10, Q801.3
unnamed: D803.3, R818.1, R821.2, U807.3
unnamed: D901.2, R902.1
unnamed: D902.1, F901.1, Q901.3, R901.1, U903.1
unnamed: D903.2, R902.2
unnamed: D1001.3, R1001.1, R1002.2, U1001.3
unnamed: D1002.3, R1013.1, R1015.2, U1006.3
unnamed: D1101.1, R1101.2
unnamed: D1102.1, R1102.2
unnamed: D1103.1, R1103.2
unnamed: D1201.2, D1204.1, R1206.1, R1210.2, R1213.2, R1216.2, R1223.1
unnamed: FB1201.2, U1201.7, U1207.7
unnamed: FB1202.2, U1201.4, U1207.4
unnamed: K401.3, U401.12
unnamed: K402.3, U401.13
unnamed: K403.3, U401.14
unnamed: K404.3, U401.15
unnamed: K405.3, U401.16
unnamed: K601.4, K601.7, R631.1
unnamed: K601.8, R629.2
unnamed: K801.7, R810.1
unnamed: K801.8, R809.2
unnamed: L201.9, U203.4
unnamed: L201.10, R210.1
unnamed: L201.11, U203.1
unnamed: L201.14, U201.4
unnamed: L201.15, R211.1
unnamed: L201.16, U201.1
unnamed: L301.2, R305.2
unnamed: L901.2, U902.2
unnamed: Q501.1, R531.2
unnamed: Q601.2, Q605.2, Q609.2, Q613.2, R603.1, R610.1, R617.1, R624.1, TP601.1, U605.6
unnamed: Q603.1, R605.1
unnamed: Q604.1, R607.1
unnamed: Q607.1, R612.1
unnamed: Q608.1, R614.1
unnamed: Q611.1, R619.1
unnamed: Q612.1, R621.1
unnamed: Q615.1, R626.1
unnamed: Q616.1, R628.1
unnamed: Q617.1, R634.1
unnamed: Q801.1, R812.1
unnamed: Q901.1, U903.3
unnamed: Q1201.1, R1202.1
unnamed: R207.1, U202.10
unnamed: R209.2, U202.24
unnamed: R301.2, U302.8
unnamed: R303.2, R304.1, U301.2
unnamed: R502.2, U501.9
unnamed: R503.2, U501.13, U505.10
unnamed: R506.1, R507.2, R510.2
unnamed: R507.1, U503.3
unnamed: R512.2, U505.9
unnamed: R522.1, R523.2, R526.2
unnamed: R523.1, U508.3
unnamed: R605.2, R607.2, U601.3
unnamed: R612.2, R614.2, U602.3
unnamed: R619.2, R621.2, U603.3
unnamed: R626.2, R628.2, U604.3
unnamed: R705.2, R707.1, U702.8
unnamed: R706.2, R708.1, U703.3
unnamed: R801.1, R806.1, R807.2, TP801.1, U802.6
unnamed: R801.2, TP802.1, U801.2, U801.6, U802.3
unnamed: R803.1, R804.1, R805.2
unnamed: R806.2, R809.1, U802.2
unnamed: R807.1, R808.2, U803.3
unnamed: R810.2, R826.2, U808.2
unnamed: R811.1, U804.1, U806.3
unnamed: R812.2, U814.3
unnamed: R813.1, R814.2, R826.1, TP805.1, U808.6
unnamed: R813.2, TP806.1, U807.2, U807.6, U808.3
unnamed: R814.1, R815.2, U803.2
unnamed: R815.1, TP803.1, U803.6, U804.4
unnamed: R820.1, U804.6, U805.6
unnamed: R820.2, U809.3
unnamed: R821.1, R822.1, R823.2, R825.2
unnamed: R824.1, TP804.1, U805.4, U810.4
unnamed: R824.2, R827.2, TP807.1, U811.4
unnamed: R825.1, RV801.2
unnamed: R827.1, U813.3
unnamed: R828.1, U810.1, U812.3
unnamed: R831.1, U810.6, U811.6
unnamed: R831.2, U815.3
unnamed: R901.2, U903.6
unnamed: R1002.1, R1003.1, R1004.2
unnamed: R1005.1, R1006.2, U1002.3
unnamed: R1005.2, TP1001.1, U1001.2, U1001.6
unnamed: R1007.1, U1003.1, U1005.3
unnamed: R1008.1, R1009.2, U1002.2
unnamed: R1008.2, TP1004.1, U1006.2, U1006.6
unnamed: R1009.1, TP1002.1, U1002.6, U1003.4
unnamed: R1014.1, U1003.6, U1004.6
unnamed: R1014.2, U1007.3
unnamed: R1015.1, R1017.1, R1018.2, R1019.2
unnamed: R1016.1, TP1003.1, U1004.4, U1008.4
unnamed: R1016.2, R1020.2, TP1005.1, U1009.4
unnamed: R1019.1, RV1001.2
unnamed: R1020.1, U1011.3
unnamed: R1021.1, U1008.1, U1010.3
unnamed: R1024.1, U1008.6, U1009.6
unnamed: R1024.2, U1012.3
unnamed: R1101.1, U1101.7
unnamed: R1102.1, U1101.8
unnamed: R1103.1, U1101.9
unnamed: R1105.1, U1101.138
unnamed: R1203.1, R1206.2, U1201.6
unnamed: R1203.2, R1209.1, U1201.2
unnamed: R1204.2, R1205.1
unnamed: R1205.2, U1202.1
unnamed: R1207.2, R1212.1, U1203.2
unnamed: R1208.1, RV1201.2
unnamed: R1208.2, R1215.1, U1205.3
unnamed: R1211.1, R1212.2, R1219.1
unnamed: R1214.1, U1206.4
unnamed: R1217.1, R1223.2, U1207.6
unnamed: R1217.2, R1224.1, U1207.2
unnamed: R1218.1, R1221.1, U1206.5
unnamed: R1221.2, R1222.2, R1225.1
unnamed: R1222.1, U1206.6
unnamed: R1225.2, R1226.2, R1227.1
unnamed: R1226.1, U1206.7
unnamed: R1228.2, X1201.1
unnamed: R1229.2, R1231.2, U1210.4
unnamed: R1230.1, U1210.2, U1212.2, U1213.2
unnamed: R1230.2, X1201.3
unnamed: U302.11, U303.5
unnamed: U302.12, U303.4
unnamed: U302.13, U303.3
unnamed: U503.6, U504.8
unnamed: U508.6, U509.8
unnamed: U804.3, U805.3
unnamed: U810.3, U811.3
unnamed: U1003.3, U1004.3
unnamed: U1008.3, U1009.3
unnamed: U1206.10, U1206.11, U1206.12, U1206.13
unnamed: U1209.2, U1210.1, U1213.15
unnamed: U1209.4, U1212.9, U1213.9
unnamed: U1212.15, U1213.10
VCCQ: C203.1, C204.1, C205.1, C206.1, C207.1, C210.1, FB201.1, L201.2, L201.7, R201.1, R202.1, R203.1, R204.1, U202.1, U202.19

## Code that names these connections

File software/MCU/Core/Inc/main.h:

/* USER CODE BEGIN Header */
/**
  ******************************************************************************
  * @file           : main.h
  * @brief          : Header for main.c file.
  *                   This file contains the common defines of the application.
  ******************************************************************************
  * @attention
  *
  * <h2><center>&copy; Copyright (c) 2021 STMicroelectronics.
  * All rights reserved.</center></h2>
  *
  * This software component is licensed by ST under Ultimate Liberty license
  * SLA0044, the "License"; You may not use this file except in compliance with
  * the License. You may obtain a copy of the License at:
  *                             www.st.com/SLA0044
  *
  ******************************************************************************
  */
/* USER CODE END Header */

/* Define to prevent recursive inclusion -------------------------------------*/
#ifndef __MAIN_H
#define __MAIN_H

#ifdef __cplusplus
extern "C" {
#endif

/* Includes ------------------------------------------------------------------*/
#include "stm32h7xx_hal.h"

#include "stm32h7xx_ll_rcc.h"
#include "stm32h7xx_ll_spi.h"
#include "stm32h7xx_ll_system.h"
#include "stm32h7xx_ll_gpio.h"
#include "stm32h7xx_ll_exti.h"
#include "stm32h7xx_ll_bus.h"
#include "stm32h7xx_ll_cortex.h"
#include "stm32h7xx_ll_utils.h"
#include "stm32h7xx_ll_pwr.h"
#include "stm32h7xx_ll_dma.h"

/* Private includes ----------------------------------------------------------*/
/* USER CODE BEGIN Includes */

/* USER CODE END Includes */

/* Exported types ------------------------------------------------------------*/
/* USER CODE BEGIN ET */

/* USER CODE END ET */

/* Exported constants --------------------------------------------------------*/
/* USER CODE BEGIN EC */

/* USER CODE END EC */

/* Exported macro ------------------------------------------------------------*/
/* USER CODE BEGIN EM */

/* USER CODE END EM */

/* Exported functions prototypes ---------------------------------------------*/
void Error_Handler(void);

/* USER CODE BEGIN EFP */

/* USER CODE END EFP */

/* Private defines -----------------------------------------------------------*/
#define IDIFF0_Pin LL_GPIO_PIN_3
#define IDIFF0_GPIO_Port GPIOE
#define SPI4_NSS_Pin LL_GPIO_PIN_4
#define SPI4_NSS_GPIO_Port GPIOE
#define IDIFF1_Pin LL_GPIO_PIN_13
#define IDIFF1_GPIO_Port GPIOC
#define SPI5_NSS_Pin LL_GPIO_PIN_6
#define SPI5_NSS_GPIO_Port GPIOF
#define nRDC_Pin LL_GPIO_PIN_10
#define nRDC_GPIO_Port GPIOF
#define TRIG_EN_Pin LL_GPIO_PIN_9
#define TRIG_EN_GPIO_Port GPIOE
#define TRIG_OUT_Pin LL_GPIO_PIN_10
#define TRIG_OUT_GPIO_Port GPIOE
#define TRIG_IN_Pin LL_GPIO_PIN_11
#define TRIG_IN_GPIO_Port GPIOE
#define TRIG_IN_EXTI_IRQn EXTI15_10_IRQn
#define CXN_REL6_Pin LL_GPIO_PIN_12
#define CXN_REL6_GPIO_Port GPIOE
#define CXN_REL5_Pin LL_GPIO_PIN_13
#define CXN_REL5_GPIO_Port GPIOE
#define CXN_REL4_Pin LL_GPIO_PIN_14
#define CXN_REL4_GPIO_Port GPIOE
#define CXN_REL3_Pin LL_GPIO_PIN_15
#define CXN_REL3_GPIO_Port GPIOE
#define CXN_REL2_Pin LL_GPIO_PIN_10
#define CXN_REL2_GPIO_Port GPIOB
#define CXN_REL1_Pin LL_GPIO_PIN_11
#define CXN_REL1_GPIO_Port GPIOB
#define nADC2_RST_Pin LL_GPIO_PIN_15
#define nADC2_RST_GPIO_Port GPIOB
#define ADC2_MDIV_Pin LL_GPIO_PIN_8
#define ADC2_MDIV_GPIO_Port GPIOD
#define nADC2_HPF_Pin LL_GPIO_PIN_9
#define nADC2_HPF_GPIO_Port GPIOD
#define ADC2_M0_Pin LL_GPIO_PIN_10
#define ADC2_M0_GPIO_Port GPIOD
#define EEPROM_WP_Pin LL_GPIO_PIN_11
#define EEPROM_WP_GPIO_Port GPIOD
#define ADC2_M1_Pin LL_GPIO_PIN_14
#define ADC2_M1_GPIO_Port GPIOD
#define IRR0_Pin LL_GPIO_PIN_8
#define IRR0_GPIO_Port GPIOG
#define VDIFF0_Pin LL_GPIO_PIN_6
#define VDIFF0_GPIO_Port GPIOC
#define VDIFF2_Pin LL_GPIO_PIN_7
#define VDIFF2_GPIO_Port GPIOC
#define VDIFF1_Pin LL_GPIO_PIN_8
#define VDIFF1_GPIO_Port GPIOC
#define IRR4_Pin LL_GPIO_PIN_9
#define IRR4_GPIO_Port GPIOA
#define IRR2_Pin LL_GPIO_PIN_10
#define IRR2_GPIO_Port GPIOA
#define IRR1_Pin LL_GPIO_PIN_11
#define IRR1_GPIO_Port GPIOA
#define IRR3_Pin LL_GPIO_PIN_12
#define IRR3_GPIO_Port GPIOA
#define SPI3_NSS_Pin LL_GPIO_PIN_15
#define SPI3_NSS_GPIO_Port GPIOA
#define ADC1_RVS1_Pin LL_GPIO_PIN_0
#define ADC1_RVS1_GPIO_Port GPIOD
#define ADC1_RVS2_Pin LL_GPIO_PIN_1
#define ADC1_RVS2_GPIO_Port GPIOD
#define MCU_DEFAULT_Pin LL_GPIO_PIN_2
#define MCU_DEFAULT_GPIO_Port GPIOD
#define ADC_SEL_Pin LL_GPIO_PIN_3
#define ADC_SEL_GPIO_Port GPIOD
#define LED_BLUE_Pin LL_GPIO_PIN_7
#define LED_BLUE_GPIO_Port GPIOD
#define LED_RED_Pin LL_GPIO_PIN_9
#define LED_RED_GPIO_Port GPIOG
#define LED_GREEN_Pin LL_GPIO_PIN_10
#define LED_GREEN_GPIO_Port GPIOG
#define DDS_LPF_Pin LL_GPIO_PIN_5
#define DDS_LPF_GPIO_Port GPIOB
#define MUX_A0_Pin LL_GPIO_PIN_6
#define MUX_A0_GPIO_Port GPIOB
#define MUX_A1_Pin LL_GPIO_PIN_7
#define MUX_A1_GPIO_Port GPIOB
#define DDS_DIV8_Pin LL_GPIO_PIN_8
#define DDS_DIV8_GPIO_Port GPIOB
#define DDS_DIV4_Pin LL_GPIO_PIN_9
#define DDS_DIV4_GPIO_Port GPIOB
#define DDS_DIV2_Pin LL_GPIO_PIN_0
#define DDS_DIV2_GPIO_Port GPIOE
#define nDDS_DIV10_Pin LL_GPIO_PIN_1
#define nDDS_DIV10_GPIO_Port GPIOE

/* USER CODE BEGIN Private defines */

/* USER CODE END Private defines */

#ifdef __cplusplus
}
#endif

#endif /* __MAIN_H */

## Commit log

2021-04-30 Star of the project
2021-04-30 Project based on https://hackaday.io/project/165409-precision-impedance-meter-asdflcr1
2021-05-01 Schematic design
2021-05-02 Footprints assigned.
2021-05-02 PCB layout
2021-05-06 Modification of the function generator schematic.
2021-05-06 Schematic
2021-05-09 Footprints
2021-05-25 Modification in schematic and PCB
2021-05-29 Fixed PCB file
2021-06-02 Schematic and PCB modifications
2021-06-03 Fixed folders. Fixes in schematics.
2021-06-03 PCB done
2021-06-10 Software development
2021-11-12 Ethernet connection and SCPI commands are working. Swapped red and green LED in the schematic.
2021-11-13 Added EEPROM and ADS8681 code.
2021-11-14 Added relays code. Moved scpi code to a different folder. Changed configuration for SPIs.
2021-11-15 Fixed bug with not switching pin but port. EEPROM and SPI3 works correctly.
2021-11-18 Started development DDS code.
2021-11-21 AD9834 is working. The problem was the SPI configuration. The SCLK must be high in idle mode, 1 edge.
2022-01-28 Converter hardware files to Kicad 6
2022-02-20 DAC7811 and DG409 work. The STM32CUBE sets the TICK_INIT_PRIORITY to 15, this is invalid for FreeRTOS, should be 0 (need to change stm32h7xx_hal_conf.h after new code generation).
2022-02-20 Added text to schematics, software development.
2022-03-13 Software development and added comments to the schematics.
2022-05-03 Software development.
2023-03-04 Converted HW files to KiCAD 7.0.
2024-07-07 Project updated
2024-07-07 README.md
2025-01-14 Typo fix.
